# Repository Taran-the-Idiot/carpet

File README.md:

# Driving Macropad

What if you had a macropad, that drives????

This is your average macropad by day but with the push of a button it turns into a toy car you can drive around on your desk. It has 4 cherry MX switches and 2 EC11 rotary encoders. For the drive motors it uses 2 N20 motors

It runs off a custom made RP2040 dev board and uses kmk firmware.

## PCB/Electronics

### Schematic

This board runs on a [custom devboard](https://github.com/Taran-the-Idiot/Taranium-RP2040) that was built for this use case that required smaller packaging. 

The motors used for the drive system are N20 motors and they are powered using the L293D motor controlelr.

For the macropad side of things, this board uses a 2x3 matrix with 4 MX keys and 2 encoders. 

In order to preserve size and packaging, a choice was made to avoid using a battery and instead the pad is run off of cable power direct from usb.

### PCB Top Side

### PCB Bottom Side

## CAD

CAD Was made in Shapr3d. It is your basic macropad case but also includes 2 wheels that go directly on the motor shafts and are lined with TPU treads for grip.

The 2 holes on the top of the case exist for the purpose of being able to reach the boot and reset buttons on the microcontroller without having to break open the case.

There are 2 fake wheels on the lower section that exist for the purpose of reducing friction between the pad and the desk due to the lower surface area.

STLs for printing can be found at the [Production/Prints](/Production/Prints/) directory.\
A STEP assembly for editing can be found at the [CAD](/CAD/) directory

## Firmware

This board uses KMK as the driving software for its functionality.

The board has 5 layers in the following format:

- Layer Swap - Used to pick the layer you wish to use
- Audio/Music Control - Used to control your music player
- Keyboard Commands - Commonly used keyboard commands
- Page Controls - Keyboard commands to open/close web pages
- Drive Control - Control how the pad drives

On the driving aspect, you can call the following functions in order to allow the pad to drive:

`forward()` - Move the pad forward\
`backward()` - Move the pad backward\
`turn_right()` - Turn the pad right\
`turn_left()` - Turn the pad left\
`stop()` - Stops both motors

Currently the functions are not tuned to specific degree turns or specific distances.\
However that would more than likely depend and differ between builds so I recommend tuning them yourself anyways to get the desired outcomes.

## BOM

|Item|Count/pack|QTY needed|Packs|Cost(AUD)|Shipping(AUD)|Total(AUD)|Total(USD)|Link|Notes|
|----|----------|----------|-----|---------|-------------|----------|----------|----|-----|
|PCB|5|1|1|4.27|2.1|6.37|4.54|JLCpcb.com||
|Switches|10|4|1|4.75|0|4.75||[source](https://www.aliexpress.com/item/1005006425450443.html?aem_p4p_detail=20260528070825379062850901470000812393&algo_pvid=6eac573d-10ba-4d88-a251-f09167cdd842&algo_exp_id=6eac573d-10ba-4d88-a251-f09167cdd842-23&pdp_ext_f=%7B%22order%22%3A%221738%22%2C%22spu_best_type%22%3A%22price%22%2C%22eval%22%3A%221%22%2C%22fromPage%22%3A%22search%22%7D&pdp_npi=6%40dis%21AUD%214.75%211.41%21%21%2122.60%216.72%21%40210328db17799773057932481e8e27%2112000037120671469%21sea%21AU%216138339337%21X%211%210%21n_tag%3A-29919%3Bd%3Ac34077ee%3Bm03_new_user%3A-29895%3BpisId%3A5000000204059337&curPageLogUid=G5LWjAJf66HO&utparam-url=scene%3Asearch%7Cquery_from%3A%7Cx_object_id%3A1005006425450443%7C_p_origin_prod%3A&search_p4p_id=20260528070825379062850901470000812393_6)||
|EC11 encoder|5|2|1|6.26|0|6.26||[source](https://www.aliexpress.com/item/1005008583446552.html?algo_pvid=c3f9c061-0fd0-4f4a-95ff-5c3e36bec910&algo_exp_id=c3f9c061-0fd0-4f4a-95ff-5c3e36bec910-1&pdp_ext_f=%7B%22order%22%3A%22890%22%2C%22spu_best_type%22%3A%22price%22%2C%22eval%22%3A%221%22%2C%22fromPage%22%3A%22search%22%7D&pdp_npi=6%40dis%21AUD%213.65%211.41%21%21%212.56%210.99%21%402103128917799774199941692e8a3b%2112000045835073062%21sea%21AU%216138339337%21X%211%210%21n_tag%3A-29919%3Bd%3Ac34077ee%3Bm03_new_user%3A-29895%3BpisId%3A5000000204059337&curPageLogUid=EXzHQf5GNgBM&utparam-url=scene%3Asearch%7Cquery_from%3A%7Cx_object_id%3A1005008583446552%7C_p_origin_prod%3A)||
|Taranium-RP2040|1|1|1|N/a|N/a|N/a|N/a|[source](https://github.com/Taran-the-Idiot/Taranium-RP2040)|Not Commercially available|
|N20 Motors|1|2|2|3.27|0|6.54||[source](https://www.aliexpress.com/item/1005009244646007.html?algo_pvid=0ee5785b-cf3b-4e6e-8182-d27c720e51fa&algo_exp_id=0ee5785b-cf3b-4e6e-8182-d27c720e51fa-1&pdp_ext_f=%7B%22order%22%3A%2292%22%2C%22eval%22%3A%221%22%2C%22fromPage%22%3A%22search%22%7D&pdp_npi=6%40dis%21AUD%216.81%211.41%21%21%2132.36%216.69%21%40210328d417799776761614649e1d07%2112000048450420463%21sea%21AU%216138339337%21X%211%210%21n_tag%3A-29919%3Bd%3Ac34077ee%3Bm03_new_user%3A-29895%3BpisId%3A5000000204059337&curPageLogUid=rc6I8zs0JHR2&utparam-url=scene%3Asearch%7Cquery_from%3A%7Cx_object_id%3A1005009244646007%7C_p_origin_prod%3A)||
|M3X5X4 Heatset Inserts|50|8|1|3.61|0|3.61||[source](https://www.aliexpress.com/item/1005003582355741.html?algo_pvid=2c3921f8-9ce4-4c2b-99d0-9135741b56ee&algo_exp_id=2c3921f8-9ce4-4c2b-99d0-9135741b56ee-1&pdp_ext_f=%7B%22order%22%3A%2266300%22%2C%22eval%22%3A%221%22%2C%22fromPage%22%3A%22search%22%7D&pdp_npi=6%40dis%21AUD%212.58%211.41%21%21%2112.25%216.69%21%402103123917799778966402429edc01%2112000026370649739%21sea%21AU%216138339337%21X%211%210%21n_tag%3A-29919%3Bd%3Ac34077ee%3Bm03_new_user%3A-29895%3BpisId%3A5000000204059337&curPageLogUid=jOwKhSwtq9o8&utparam-url=scene%3Asearch%7Cquery_from%3A%7Cx_object_id%3A1005003582355741%7C_p_origin_prod%3A)||
|L293D|5|1|1|3.59|0|3.59||[source](https://www.aliexpress.com/item/1005010400118009.html?algo_pvid=1d5a83a6-2e25-4fc1-83b2-14fbf2c2c82a&algo_exp_id=1d5a83a6-2e25-4fc1-83b2-14fbf2c2c82a-0&pdp_ext_f=%7B%22order%22%3A%22157%22%2C%22spu_best_type%22%3A%22price%22%2C%22eval%22%3A%221%22%2C%22fromPage%22%3A%22search%22%7D&pdp_npi=6%40dis%21AUD%213.58%211.41%21%21%2117.01%216.69%21%402103123917799778352857051edb9c%2112000052283568710%21sea%21AU%216138339337%21X%211%210%21n_tag%3A-29919%3Bd%3Ac34077ee%3Bm03_new_user%3A-29895%3BpisId%3A5000000204059337&curPageLogUid=J6RLGmCUfqa4&utparam-url=scene%3Asearch%7Cquery_from%3A%7Cx_object_id%3A1005010400118009%7C_p_origin_prod%3A)||
|M3x16mm Screw|50|2|1|3.22|0|3.22||[source](https://www.aliexpress.com/item/4001199728978.html?algo_pvid=062e496a-bdc5-4c1c-89d0-1ab4981b1094&aem_p4p_detail=202605282216169273763264068760001401936&algo_exp_id=062e496a-bdc5-4c1c-89d0-1ab4981b1094-11&pdp_ext_f=%7B%22order%22%3A%2215938%22%2C%22eval%22%3A%221%22%2C%22fromPage%22%3A%22search%22%7D&pdp_npi=6%40dis%21AUD%211.91%211.40%21%21%211.35%210.99%21%4021030a4b17800317766066984e5569%2110000015289904574%21sea%21AU%216138339337%21X%211%210%21n_tag%3A-29919%3Bd%3Ac34077ee%3Bm03_new_user%3A-29895%3BpisId%3A5000000204059337&curPageLogUid=J1RTS7lEbgbp&utparam-url=scene%3Asearch%7Cquery_from%3A%7Cx_object_id%3A4001199728978%7C_p_origin_prod%3A&search_p4p_id=202605282216169273763264068760001401936_4)||
|M3x25mm Screw|50|2|1|4|0|4||[source](https://www.aliexpress.com/item/4001199728978.html?algo_pvid=062e496a-bdc5-4c1c-89d0-1ab4981b1094&aem_p4p_detail=202605282216169273763264068760001401936&algo_exp_id=062e496a-bdc5-4c1c-89d0-1ab4981b1094-11&pdp_ext_f=%7B%22order%22%3A%2215938%22%2C%22eval%22%3A%221%22%2C%22fromPage%22%3A%22search%22%7D&pdp_npi=6%40dis%21AUD%211.91%211.40%21%21%211.35%210.99%21%4021030a4b17800317766066984e5569%2110000015289904574%21sea%21AU%216138339337%21X%211%210%21n_tag%3A-29919%3Bd%3Ac34077ee%3Bm03_new_user%3A-29895%3BpisId%3A5000000204059337&curPageLogUid=J1RTS7lEbgbp&utparam-url=scene%3Asearch%7Cquery_from%3A%7Cx_object_id%3A4001199728978%7C_p_origin_prod%3A&search_p4p_id=202605282216169273763264068760001401936_4)||
|M3x6mm Screws|50|4|1|2.55|0|2.55||[source](https://www.aliexpress.com/item/4001199728978.html?algo_pvid=062e496a-bdc5-4c1c-89d0-1ab4981b1094&aem_p4p_detail=202605282216169273763264068760001401936&algo_exp_id=062e496a-bdc5-4c1c-89d0-1ab4981b1094-11&pdp_ext_f=%7B%22order%22%3A%2215938%22%2C%22eval%22%3A%221%22%2C%22fromPage%22%3A%22search%22%7D&pdp_npi=6%40dis%21AUD%211.91%211.40%21%21%211.35%210.99%21%4021030a4b17800317766066984e5569%2110000015289904574%21sea%21AU%216138339337%21X%211%210%21n_tag%3A-29919%3Bd%3Ac34077ee%3Bm03_new_user%3A-29895%3BpisId%3A5000000204059337&curPageLogUid=J1RTS7lEbgbp&utparam-url=scene%3Asearch%7Cquery_from%3A%7Cx_object_id%3A4001199728978%7C_p_origin_prod%3A&search_p4p_id=202605282216169273763264068760001401936_5)||
|3D Printed Parts||13||N/A|N/A|||YOUR PRINTER|Cost depends on filament used.|
|Total||||||40.89|29.2993206|||

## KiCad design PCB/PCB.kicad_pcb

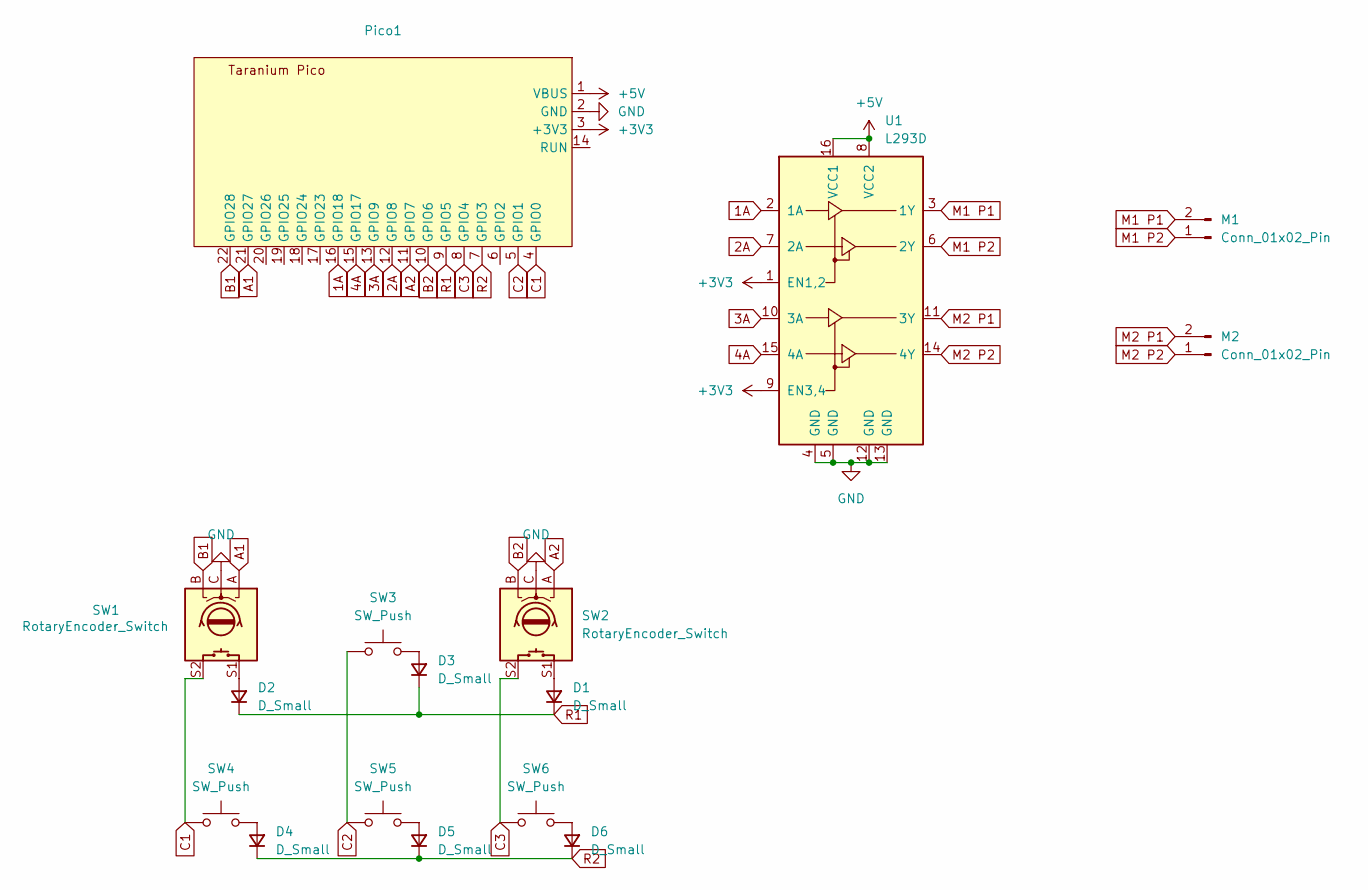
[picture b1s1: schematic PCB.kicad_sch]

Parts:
D1, D2, D3, D4, D5, D6: D_Small; D_DO-35_SOD27_P7.62mm_Horizontal
M1, M2: Conn_01x02_Pin; PinHeader_1x02_P2.54mm_Vertical
Pico1: Taranium_Pico
SW1, SW2: RotaryEncoder_Switch; RotaryEncoder_Alps_EC11E-Switch_Vertical_H20mm
SW3, SW4, SW5, SW6: SW_Push; SW_Cherry_MX_1.00u_PCB
U1: L293D; DIP-16_W7.62mm

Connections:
1A: Pico1.16 (GPIO18), U1.2 (1A)
2A: Pico1.12 (GPIO8), U1.7 (2A)
3A: Pico1.13 (GPIO9), U1.10 (3A)
4A: Pico1.15 (GPIO17), U1.15 (4A)
+3V3: Pico1.3 (+3V3), U1.1 (EN1,2), U1.9 (EN3,4)
+5V: Pico1.1 (VBUS), U1.8 (VCC2), U1.16 (VCC1)
A1: Pico1.21 (GPIO27), SW1.A
A2: Pico1.11 (GPIO7), SW2.A
B1: Pico1.22 (GPIO28), SW1.B
B2: Pico1.10 (GPIO6), SW2.B
C1: Pico1.4 (GPIO0), SW1.S2, SW4.1
C2: Pico1.5 (GPIO1), SW3.1, SW5.1
C3: Pico1.8 (GPIO4), SW2.S2, SW6.1
GND: Pico1.2 (GND), SW1.C, SW2.C, U1.4 (GND), U1.5 (GND), U1.12 (GND), U1.13 (GND)
M1 P1: M1.2, U1.3 (1Y)
M1 P2: M1.1, U1.6 (2Y)
M2 P1: M2.2, U1.11 (3Y)
M2 P2: M2.1, U1.14 (4Y)
unnamed: D1.2 (A), SW2.S1
unnamed: D2.2 (A), SW1.S1
unnamed: D3.2 (A), SW3.2
unnamed: D4.2 (A), SW4.2
unnamed: D5.2 (A), SW5.2
unnamed: D6.2 (A), SW6.2
R1: D1.1 (K), D2.1 (K), D3.1 (K), Pico1.9 (GPIO5)
R2: D4.1 (K), D5.1 (K), D6.1 (K), Pico1.7 (GPIO3)

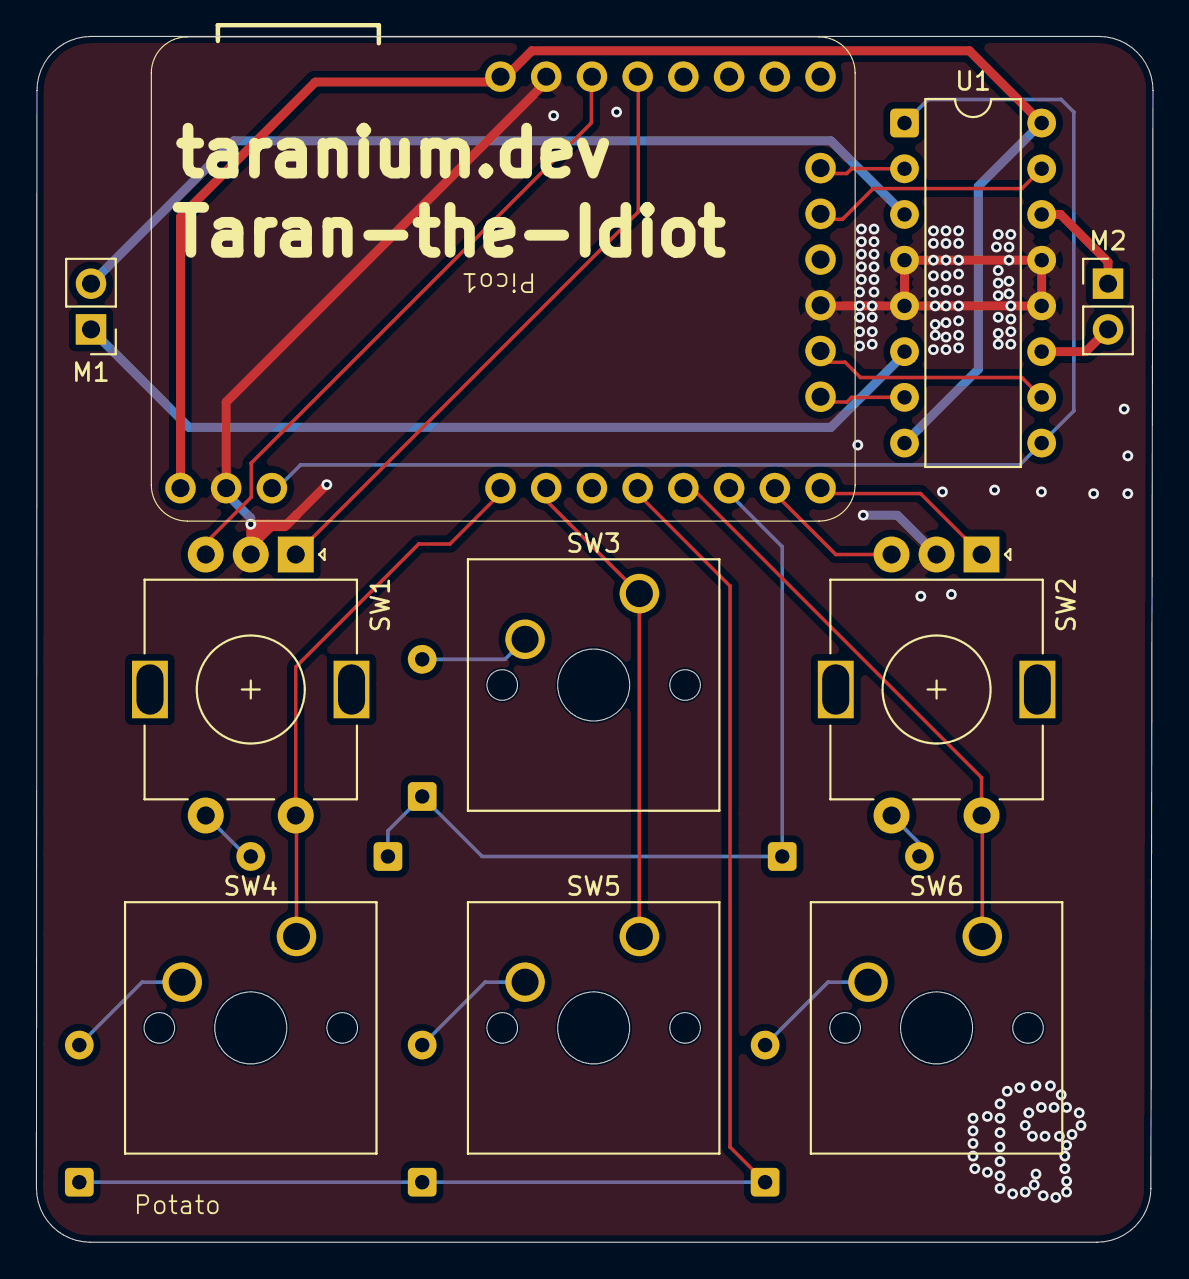
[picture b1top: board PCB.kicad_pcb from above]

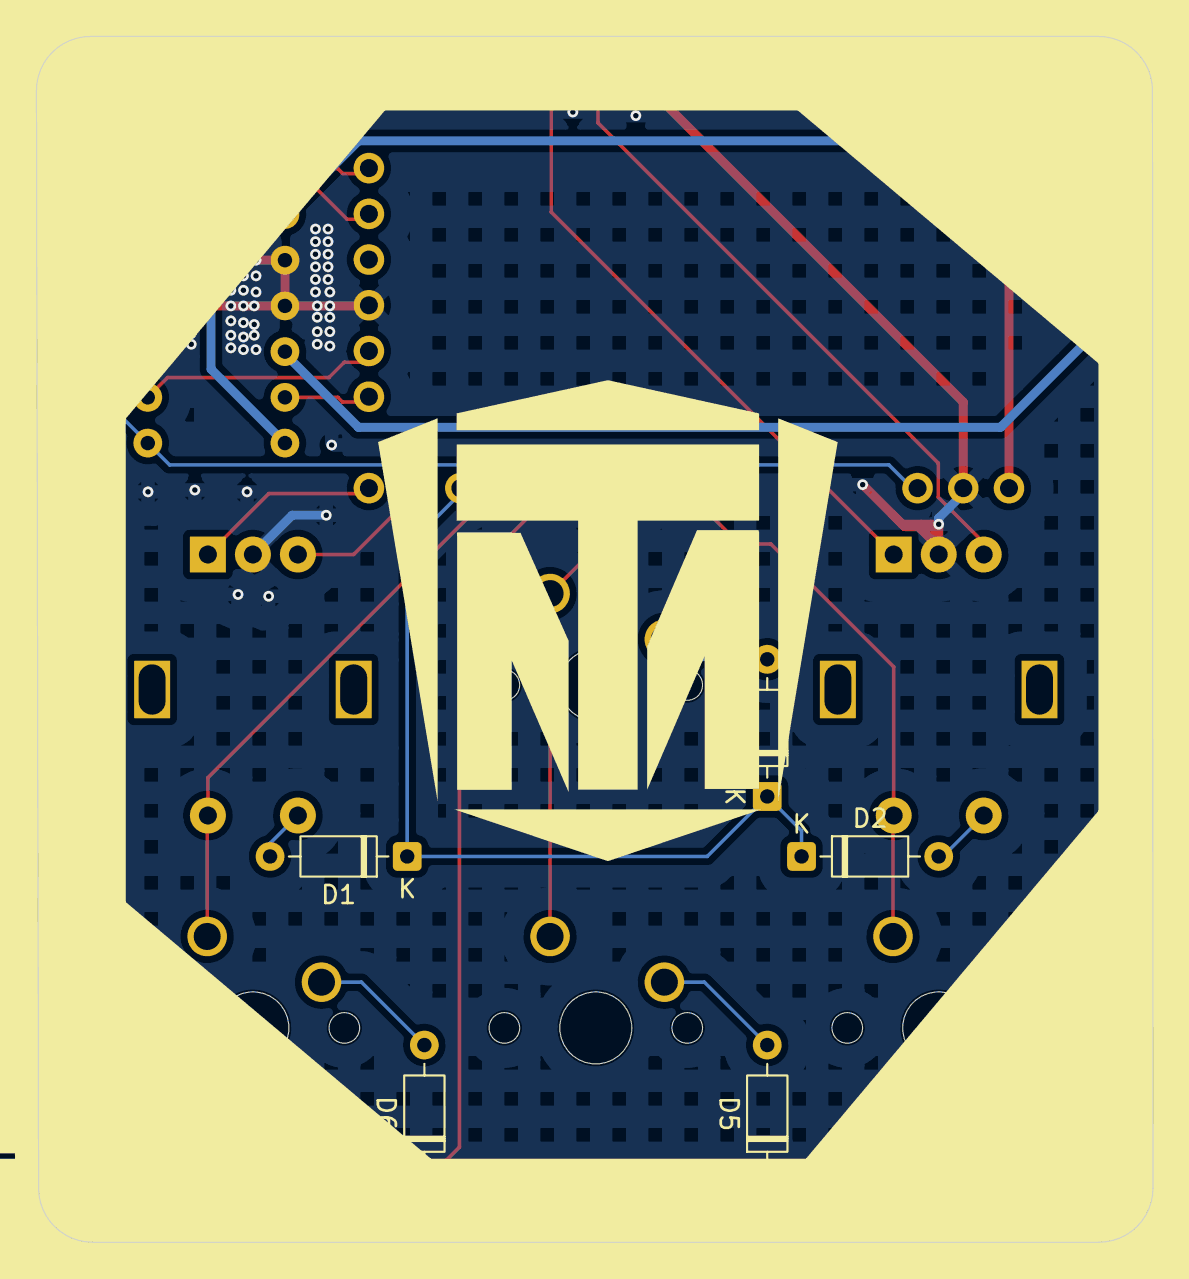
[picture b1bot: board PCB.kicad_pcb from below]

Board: 2 copper layers, 62.0 x 67.0 mm, 16 parts (6 on the bottom side), 26 nets.

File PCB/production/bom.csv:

Designator,Footprint,Quantity,Value,LCSC Part #
"D1, D2, D3, D4, D5, D6",D_DO-35_SOD27_P7.62mm_Horizontal,6,D_Small,
"M1, M2",PinHeader_1x02_P2.54mm_Vertical,2,Conn_01x02_Pin,
PICO1,Taranium_Pico,1,~,
"SW1, SW2",RotaryEncoder_Alps_EC11E-Switch_Vertical_H20mm,2,RotaryEncoder_Switch,
"SW3, SW4, SW5, SW6",SW_Cherry_MX_1.00u_PCB,4,SW_Push,
U1,DIP-16_W7.62mm,1,L293D,

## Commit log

2026-05-02 journal and readme
2026-05-02 open sauce is cool
2026-05-02 commit ma balls
2026-05-02 gitignore work
2026-05-02 wheels
2026-05-03 commit journal
2026-05-21 bleh
2026-05-21 gitingore
2026-05-22 potato
2026-05-26 commit again
2026-05-26 mojkljk
2026-05-27 kmk stinky
2026-05-28 potato2
2026-05-29 ima bomb you
2026-05-29 radme
2026-05-29 monkey
2026-06-18 cpmmoit
